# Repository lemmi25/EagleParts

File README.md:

Eagle Parts
===========

In this repo you will find a collection of all my designed PCBs.

# Docu

You can find the [Docu here](https://lemmi25.github.io/EagleParts/).

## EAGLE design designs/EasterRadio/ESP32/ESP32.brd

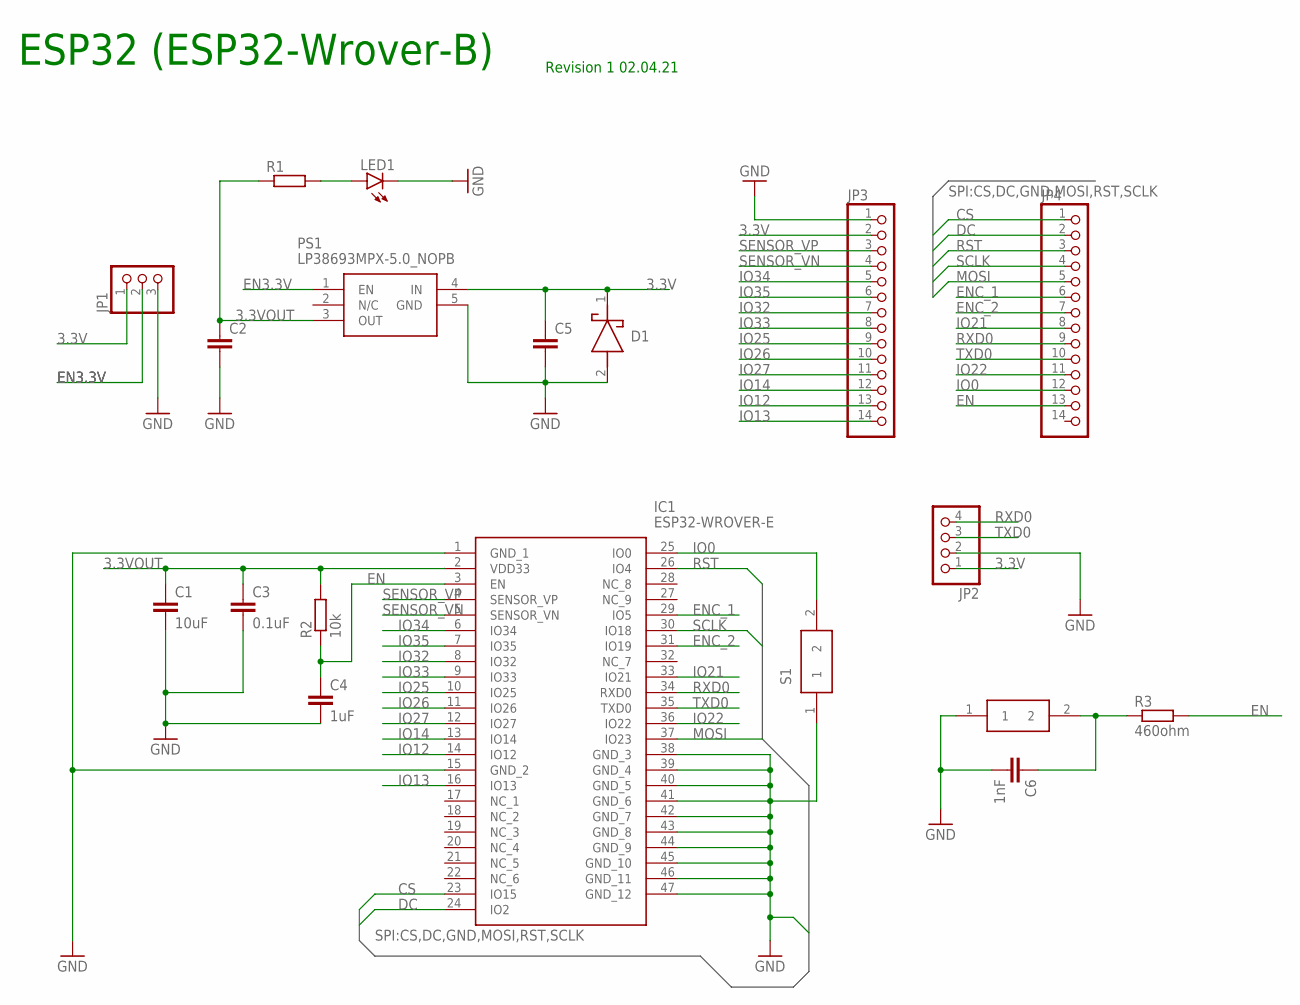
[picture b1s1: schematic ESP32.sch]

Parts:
C1: 10uF; C1206
C2, C5: C-EUC0805; C0805
C3: 0.1uF; C0805
C4: 1uF; C0805
C6: 1nF; C0805
D1: LSM115JE3_TR13; DIOM5436X330N
IC1: ESP32-WROVER-E; ESP32WROVERBM213DH6464PC3Q0
JP1: PINHD-1X3; 1X03
JP2: PINHD-1X4; 1X04
JP3, JP4: PINHD-1X14; 1X14
LED1: LED_1206SMT1206; 1206
PS1: LP38693MPX-5.0_NOPB; SOT150P700X160-5N
R1: R-EU_R0805; R0805
R2: 10k; R0805
R3: 460ohm; R0805
S1, S2: FSMSMTR; FSMSM

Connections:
3.3V: C5.1, D1.1 (K), JP1.1, JP2.1, JP3.2, PS1.4 (IN)
3.3VOUT: C1.1, C2.1, C3.1, IC1.2 (VDD33), PS1.3 (OUT), R1.1, R2.2
CS: IC1.23 (IO15), JP4.1
DC: IC1.24 (IO2), JP4.2
EN: C4.1, IC1.3 (EN), JP4.13, R2.1, R3.2
EN3.3V: JP1.2, PS1.1 (EN)
ENC_1: IC1.29 (IO5), JP4.6
ENC_2: IC1.31 (IO19), JP4.7
EN_1: C6.1, R3.1, S2.2
GND: C1.2, C2.2, C3.2, C4.2, C5.2, C6.2, D1.2 (A), IC1.1 (GND_1), IC1.15 (GND_2), IC1.38 (GND_3), IC1.39 (GND_4), IC1.40 (GND_5), IC1.41 (GND_6), IC1.42 (GND_7), IC1.43 (GND_8), IC1.44 (GND_9), IC1.45 (GND_10), IC1.46 (GND_11), IC1.47 (GND_12), JP1.3, JP2.2, JP3.1, LED1.C, PS1.5 (GND), S1.1, S2.1
IO0: IC1.25 (IO0), JP4.12, S1.2
IO12: IC1.14 (IO12), JP3.13
IO13: IC1.16 (IO13), JP3.14
IO14: IC1.13 (IO14), JP3.12
IO21: IC1.33 (IO21), JP4.8
IO22: IC1.36 (IO22), JP4.11
IO25: IC1.10 (IO25), JP3.9
IO26: IC1.11 (IO26), JP3.10
IO27: IC1.12 (IO27), JP3.11
IO32: IC1.8 (IO32), JP3.7
IO33: IC1.9 (IO33), JP3.8
IO34: IC1.6 (IO34), JP3.5
IO35: IC1.7 (IO35), JP3.6
MOSI: IC1.37 (IO23), JP4.5
unnamed: LED1.A, R1.2
RST: IC1.26 (IO4), JP4.3
RXD0: IC1.34 (RXD0), JP2.4, JP4.9
SCLK: IC1.30 (IO18), JP4.4
SENSOR_VN: IC1.5 (SENSOR_VN), JP3.4
SENSOR_VP: IC1.4 (SENSOR_VP), JP3.3
TXD0: IC1.35 (TXD0), JP2.3, JP4.10

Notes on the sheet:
ESP32 (ESP32-Wrover-B)
Revision 1 02.04.21

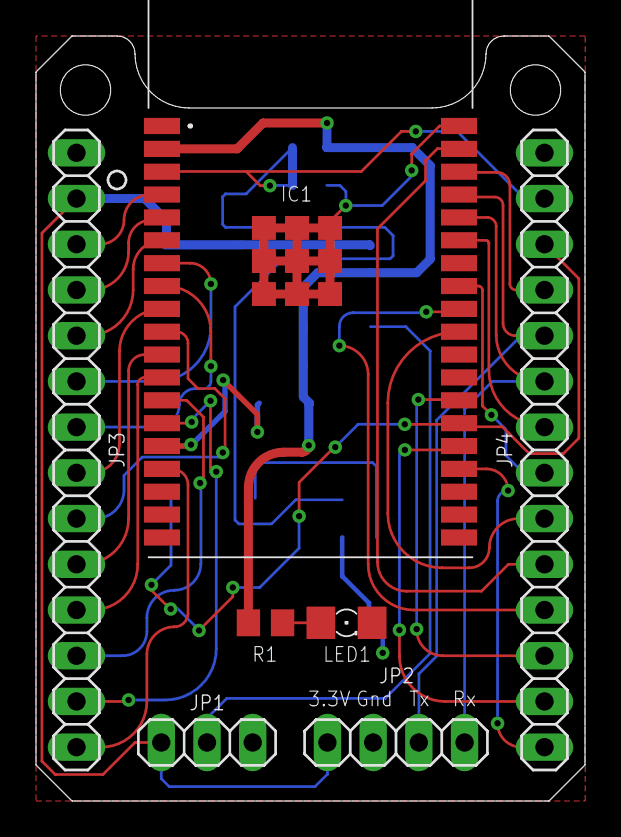
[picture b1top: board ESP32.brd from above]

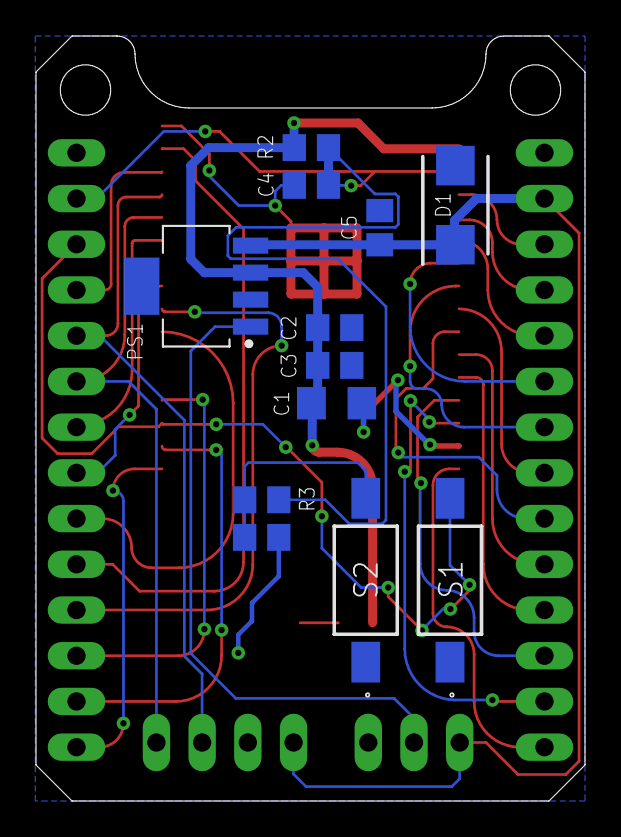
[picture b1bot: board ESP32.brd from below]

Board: 2 copper layers, 30.5 x 42.5 mm, 19 parts (12 on the bottom side), 31 nets.

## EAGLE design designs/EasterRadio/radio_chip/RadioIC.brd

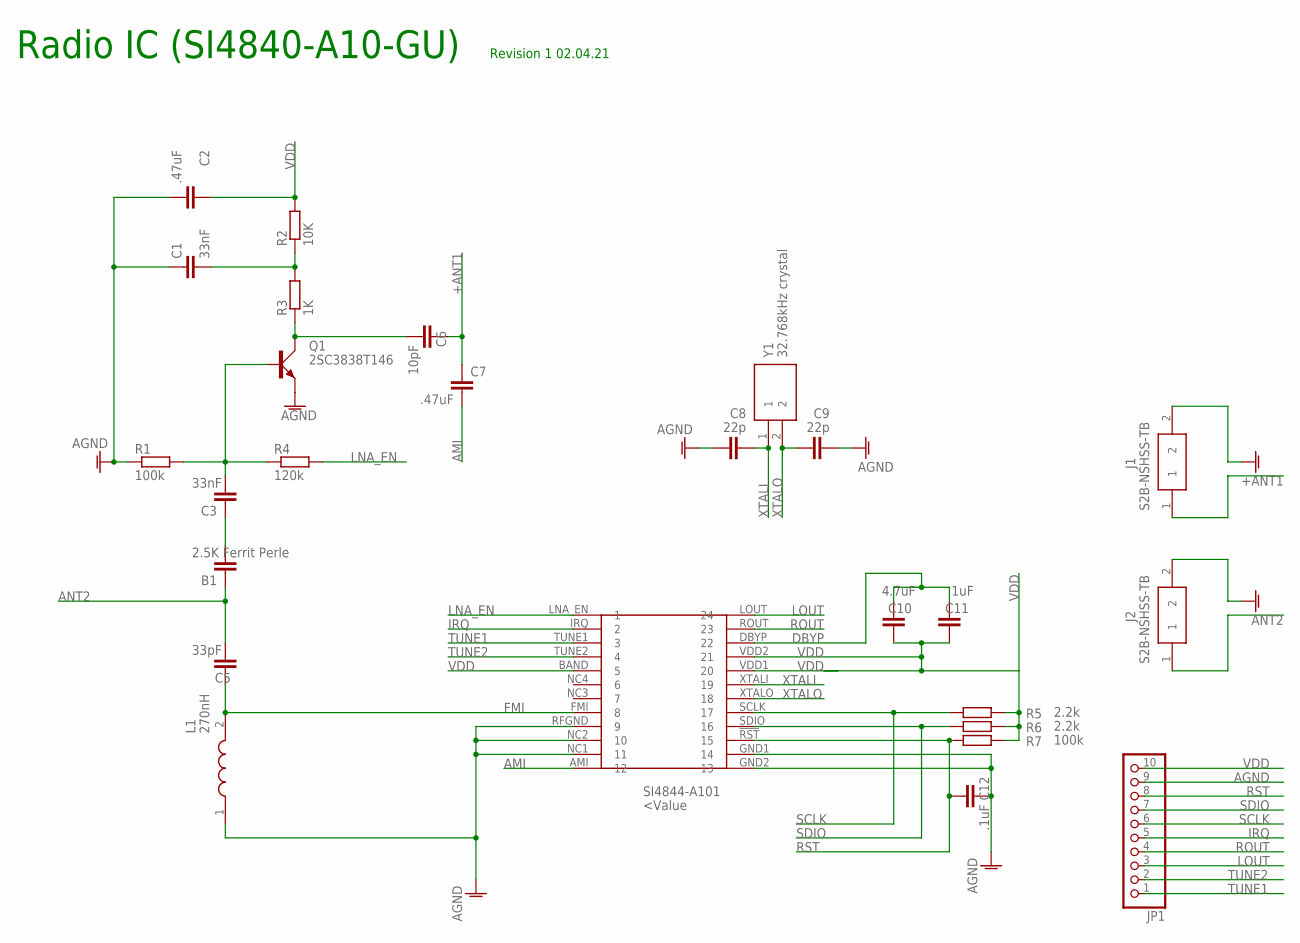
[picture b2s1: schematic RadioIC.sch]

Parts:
B1: 2.5K Ferrit Perle; C0805
C1, C3: 33nF; C1206
C2, C7: .47uF; C0805
C5: 33pF; C0805
C6: 10pF; C0805
C8, C9: 22p; C0805
C10: 4.7uF; C1206
C11: 1uF; C0805
C12: .1uF; C0805
J1, J2: S2B-NSHSS-TB; SM02B-NSHSS-TB
JP1: PINHD-1X10; 1X10
L1: 270nH; LQW2UAS12NG00L
Q1: 2SC3838T146; SC59
R1, R7: 100k; R0805
R2: 10K; R1206
R3: 1K; R1206
R4: 120k; R0805
R5, R6: 2.2k; R0805
SI4844-A101: SI4840-A10-GU; SSOP
Y1: 32.768kHz crystal; CM7VT1A32768KHZ125PF10PPMTBQC

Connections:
+ANT1: C6.1, C7.1, J1.1
AGND: C1.1, C2.2, C8.1, C9.2, C12.1, J1.2, J2.2, JP1.9, L1.1, Q1.E, R1.1, SI4844-A101.GND1 (14), SI4844-A101.GND2 (13), SI4844-A101.NC1 (11), SI4844-A101.NC2 (10), SI4844-A101.RFGND (9)
AMI: C7.2, SI4844-A101.AMI (12)
ANT2: B1.1, C5.2, J2.1
DBYP: C10.2, C11.2, SI4844-A101.DBYP (22)
FMI: C5.1, L1.2, SI4844-A101.FMI (8)
IRQ: JP1.5, SI4844-A101.IRQ (2)
LNA_EN: R4.2, SI4844-A101.LNA_EN (1)
LOUT: JP1.3, SI4844-A101.LOUT (24)
unnamed: B1.2, C3.1
unnamed: C3.2, Q1.B, R1.2, R4.1
unnamed: C6.2, Q1.C, R3.1
unnamed: C1.2, R2.1, R3.2
ROUT: JP1.4, SI4844-A101.ROUT (23)
RST: C12.2, JP1.8, R7.1, SI4844-A101.!RST (15)
SCLK: JP1.6, R5.1, SI4844-A101.SCLK (17)
SDIO: JP1.7, R6.1, SI4844-A101.SDIO (16)
TUNE1: JP1.1, SI4844-A101.TUNE1 (3)
TUNE2: JP1.2, SI4844-A101.TUNE2 (4)
VDD: C2.1, C10.1, C11.1, JP1.10, R2.2, R5.2, R6.2, R7.2, SI4844-A101.BAND (5), SI4844-A101.VDD1 (20), SI4844-A101.VDD2 (21)
XTALI: C8.2, SI4844-A101.XTALI (19), Y1.1
XTALO: C9.1, SI4844-A101.XTALO (18), Y1.2

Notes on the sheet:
Radio IC (SI4840-A10-GU)
Revision 1 02.04.21

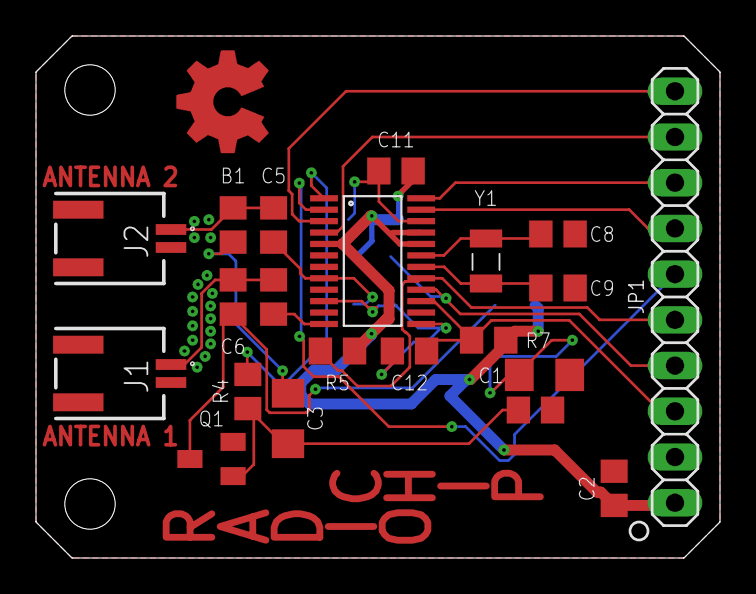
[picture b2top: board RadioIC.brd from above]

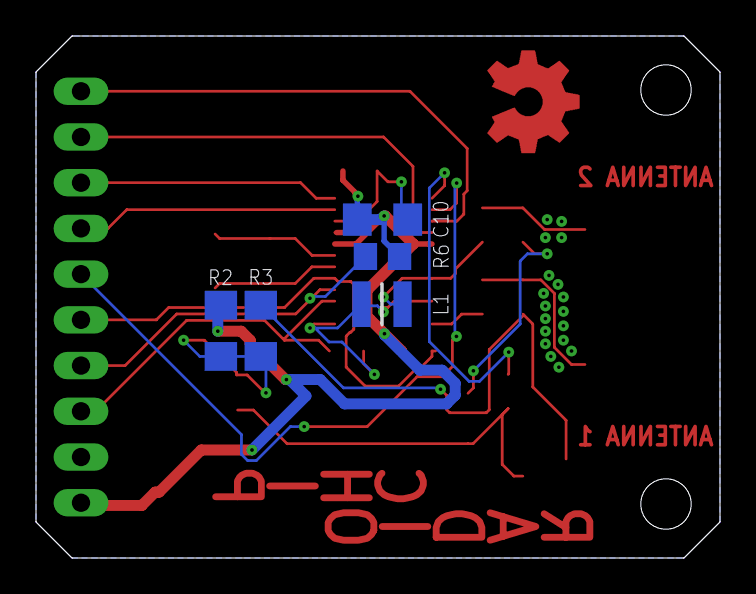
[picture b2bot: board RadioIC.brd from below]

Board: 2 copper layers, 38.0 x 29.0 mm, 26 parts (5 on the bottom side), 22 nets.

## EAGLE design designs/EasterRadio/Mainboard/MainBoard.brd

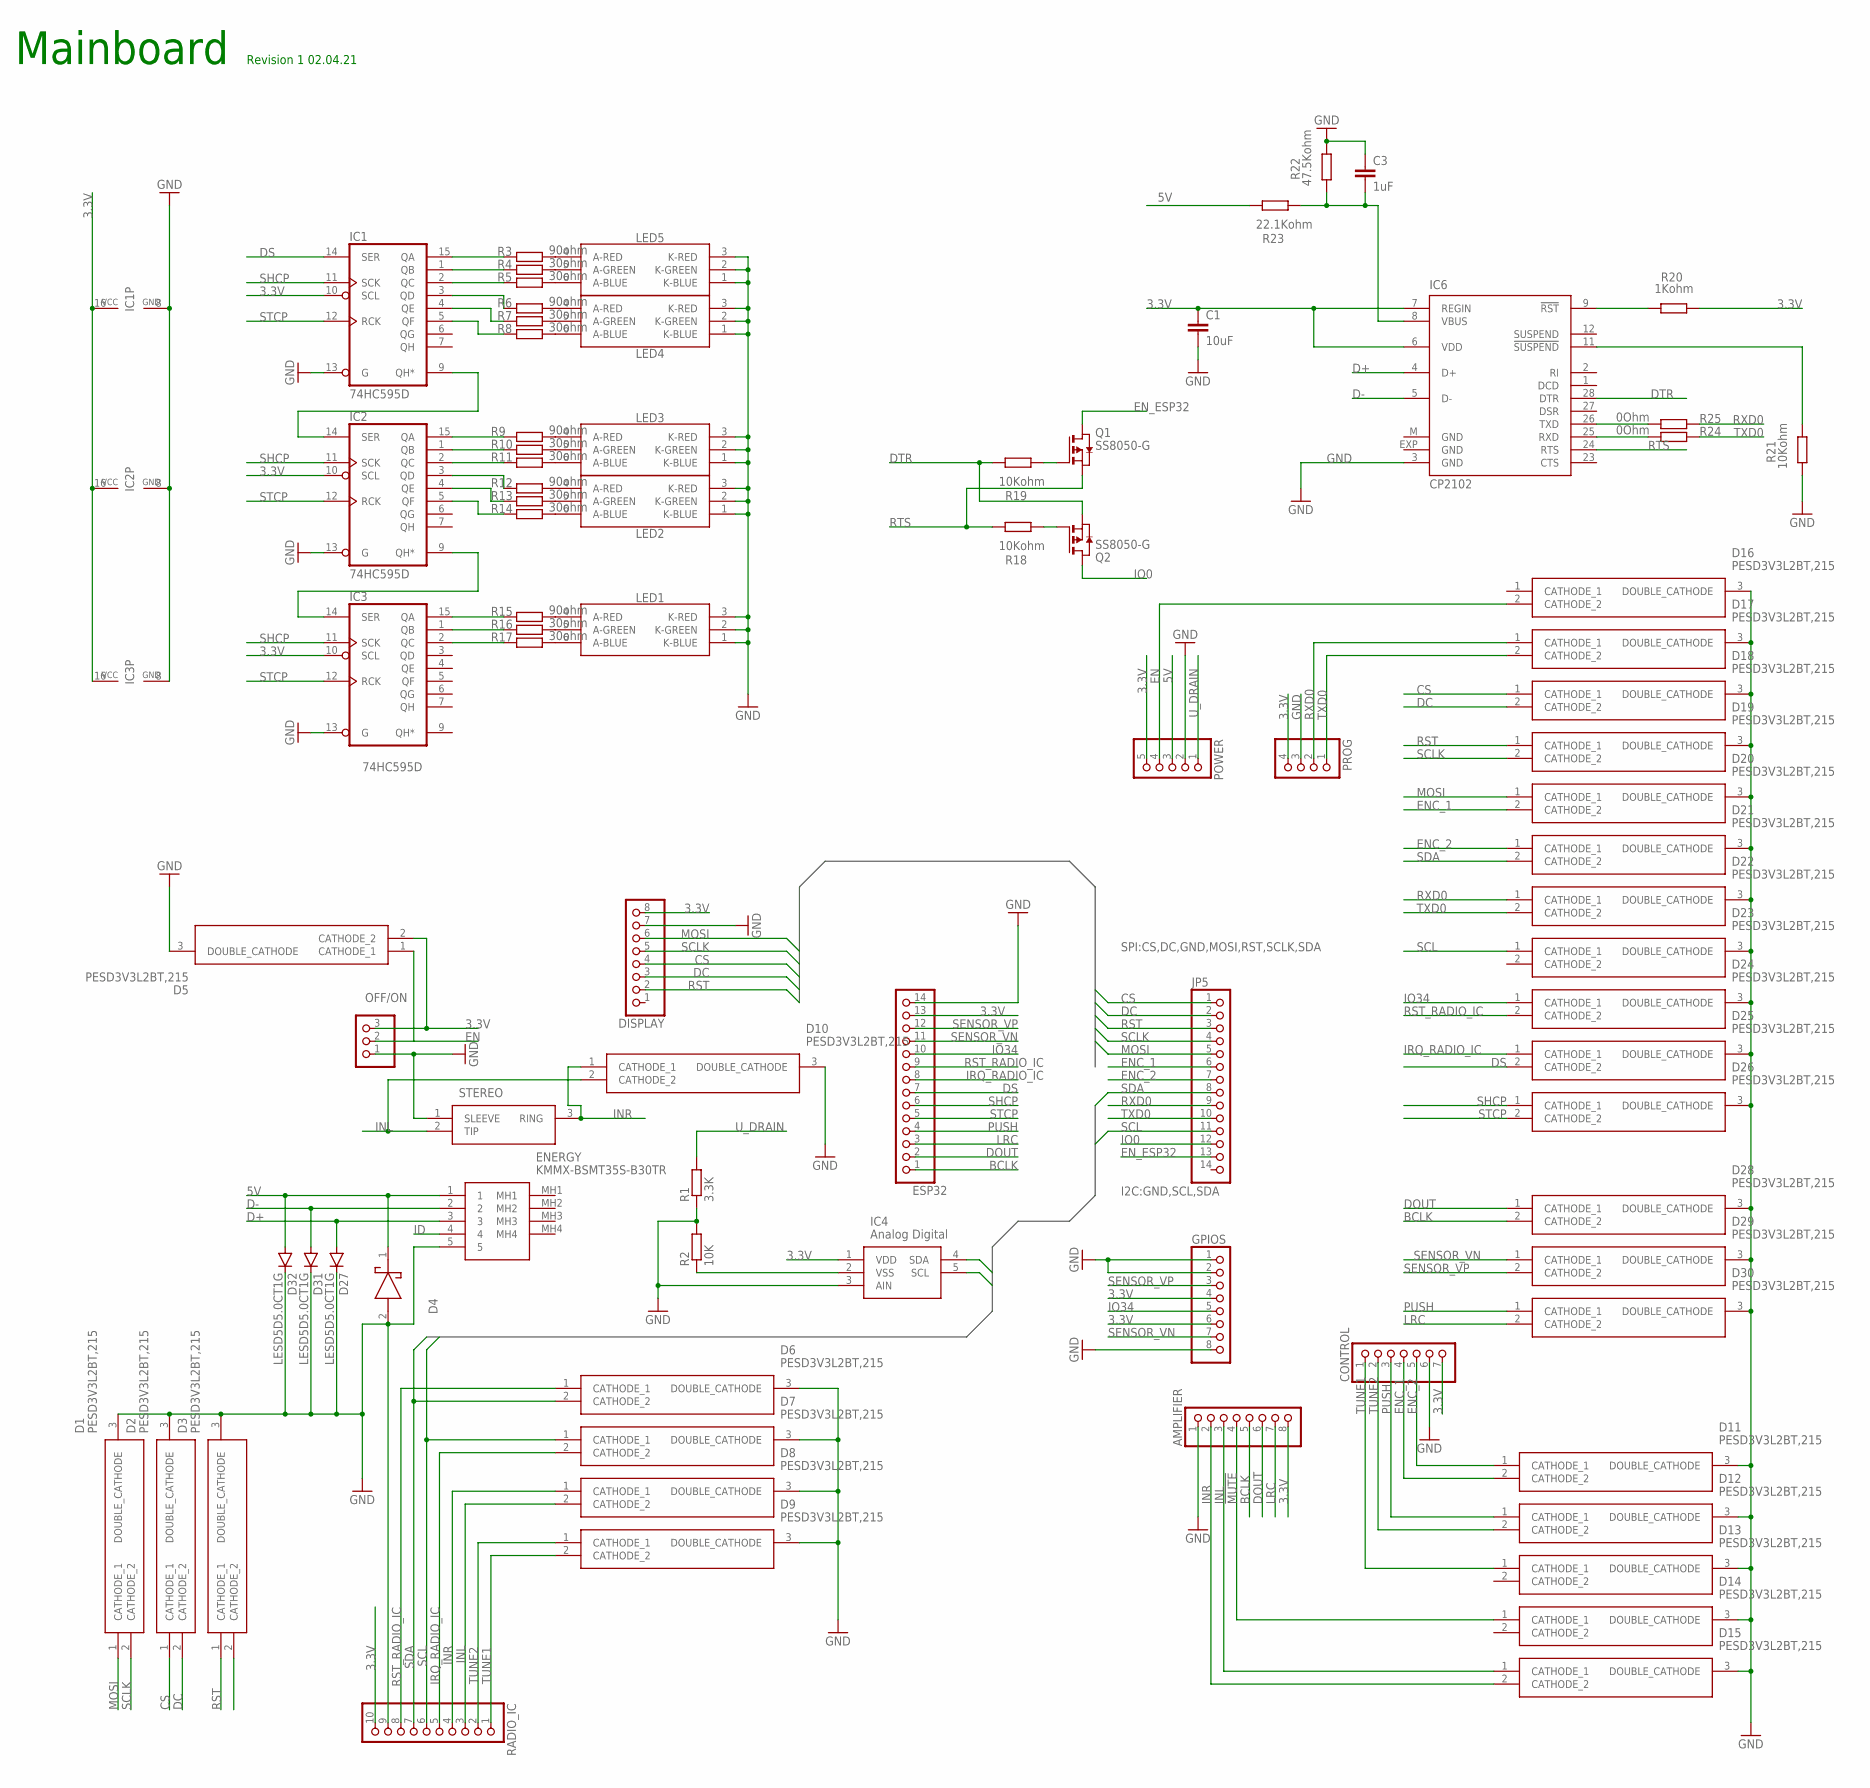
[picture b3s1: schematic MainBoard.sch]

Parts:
AMPLIFIER: PINHD-1X8; 1X08
C1: 10uF; C0805
C3: 1uF; C0805
CONTROL: PINHD-1X7; 1X07
D1, D2, D3, D5, D6, D7, D8, D9, D10, D11, D12, D13, D14, D15, D16, D17, D18, D19, D20, D21, D22, D23, D24, D25, D26, D28, D29, D30: PESD3V3L2BT,215; SOT95P230X110-3N
D4: LSM115JE3_TR13; DIOM5436X330N
D27, D31, D32: LESD5D5.0CT1G; SOD523
DISPLAY: PINHD-1X8; 1X08
ENERGY: KMMX-BSMT35S-B30TR; KMMXBSMT35SB30TR
ESP32: PINHD-1X14; 1X14
GPIOS: PINHD-1X8; 1X08
IC1, IC2, IC3: 74HC595D; SO16
IC4: Analog Digital; SOT95P280X145-5N
IC6: CP2102; MLP28
JP5: PINHD-1X14; 1X14
LED1, LED2, LED3, LED4, LED5: CLY6D-FKC-CK1N1D1BB7D3D3; PLCC6
OFF/ON: PINHD-1X3; 1X03
POWER: PINHD-1X5; 1X05
PROG: PINHD-1X4; 1X04
Q1, Q2: SS8050-G; SOT-23
R1: 3.3K; R0603
R2: 10K; R0603
R3, R6, R9, R12, R15: 90ohm; R0402
R4, R5, R7, R8, R10, R11, R13, R14, R16, R17: 30ohm; R0402
R18, R19: 10Kohm; R0402
R20: 1Kohm; R0402
R21: 10Kohm; R0805
R22: 47.5Kohm; R0402
R23: 22.1Kohm; R0402
R24, R25: 0Ohm; R0603
RADIO_IC: PINHD-1X10; 1X10
STEREO: SJ-3523-SMT-TR; SJ3523SMTTR

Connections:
3.3V: AMPLIFIER.8, C1.1, CONTROL.7, D5.2 (CATHODE_2), DISPLAY.8, ESP32.13, GPIOS.4, GPIOS.6, IC1.10 (SCL), IC1.16 (VCC), IC2.10 (SCL), IC2.16 (VCC), IC3.10 (SCL), IC3.16 (VCC), IC4.1 (VDD), IC6.6 (VDD), IC6.7 (REGIN), OFF/ON.3, POWER.5, PROG.4, R20.2, RADIO_IC.10
5V: D4.1 (K), D32.A, ENERGY.1, POWER.3, R23.1
!MUTE: AMPLIFIER.4, D14.1 (CATHODE_1)
BCLK: AMPLIFIER.5, D28.2 (CATHODE_2), ESP32.1
CS: D2.1 (CATHODE_1), D18.1 (CATHODE_1), DISPLAY.4, JP5.1
D+: D27.A, ENERGY.3, IC6.4 (D+)
D-: D31.A, ENERGY.2, IC6.5 (D-)
DC: D2.2 (CATHODE_2), D18.2 (CATHODE_2), DISPLAY.3, JP5.2
DOUT: AMPLIFIER.6, D28.1 (CATHODE_1), ESP32.2
DS: D25.2 (CATHODE_2), ESP32.7, IC1.14 (SER)
DTR: IC6.28 (DTR), Q2.2 (S), R19.1
EN: D5.1 (CATHODE_1), D16.2 (CATHODE_2), OFF/ON.2, POWER.4
ENC_1: CONTROL.4, D11.2 (CATHODE_2), D20.2 (CATHODE_2), JP5.6
ENC_2: CONTROL.5, D11.1 (CATHODE_1), D21.1 (CATHODE_1), JP5.7
EN_ESP32: JP5.13, Q1.1 (D)
GND: AMPLIFIER.1, C1.2, C3.1, CONTROL.6, D1.3 (DOUBLE_CATHODE), D2.3 (DOUBLE_CATHODE), D3.3 (DOUBLE_CATHODE), D4.2 (A), D5.3 (DOUBLE_CATHODE), D6.3 (DOUBLE_CATHODE), D7.3 (DOUBLE_CATHODE), D8.3 (DOUBLE_CATHODE), D9.3 (DOUBLE_CATHODE), D10.3 (DOUBLE_CATHODE), D11.3 (DOUBLE_CATHODE), D12.3 (DOUBLE_CATHODE), D13.3 (DOUBLE_CATHODE), D14.3 (DOUBLE_CATHODE), D15.3 (DOUBLE_CATHODE), D16.3 (DOUBLE_CATHODE), D17.3 (DOUBLE_CATHODE), D18.3 (DOUBLE_CATHODE), D19.3 (DOUBLE_CATHODE), D20.3 (DOUBLE_CATHODE), D21.3 (DOUBLE_CATHODE), D22.3 (DOUBLE_CATHODE), D23.3 (DOUBLE_CATHODE), D24.3 (DOUBLE_CATHODE), D25.3 (DOUBLE_CATHODE), D26.3 (DOUBLE_CATHODE), D27.C, D28.3 (DOUBLE_CATHODE), D29.3 (DOUBLE_CATHODE), D30.3 (DOUBLE_CATHODE), D31.C, D32.C, DISPLAY.7, ENERGY.5, ESP32.14, GPIOS.1, GPIOS.2, GPIOS.8, IC1.8 (GND), IC1.13 (G), IC2.8 (GND), IC2.13 (G), IC3.8 (GND), IC3.13 (G), IC4.3 (AIN), IC6.3 (GND), IC6.EXP (GND), IC6.M (GND), LED1.1 (K-BLUE), LED1.2 (K-GREEN), LED1.3 (K-RED), LED2.1 (K-BLUE), LED2.2 (K-GREEN), LED2.3 (K-RED), LED3.1 (K-BLUE), LED3.2 (K-GREEN), LED3.3 (K-RED), LED4.1 (K-BLUE), LED4.2 (K-GREEN), LED4.3 (K-RED), LED5.1 (K-BLUE), LED5.2 (K-GREEN), LED5.3 (K-RED), OFF/ON.1, POWER.2, PROG.3, R1.1, R2.2, R21.1, R22.2, RADIO_IC.9, STEREO.1 (SLEEVE)
ID: ENERGY.4
INL: AMPLIFIER.3, D8.2 (CATHODE_2), D10.2 (CATHODE_2), D15.1 (CATHODE_1), RADIO_IC.3, STEREO.2 (TIP)
INR: AMPLIFIER.2, D8.1 (CATHODE_1), D10.1 (CATHODE_1), D15.2 (CATHODE_2), RADIO_IC.4, STEREO.3 (RING)
IO0: JP5.12, Q2.1 (D)
IO34: D24.1 (CATHODE_1), ESP32.10, GPIOS.5
IRQ_RADIO_IC: D7.2 (CATHODE_2), D25.1 (CATHODE_1), ESP32.8, RADIO_IC.5
LRC: AMPLIFIER.7, D30.2 (CATHODE_2), ESP32.3
MOSI: D1.1 (CATHODE_1), D20.1 (CATHODE_1), DISPLAY.6, JP5.5
unnamed: Q2.3 (G), R18.2
unnamed: Q1.3 (G), R19.2
unnamed: LED2.4 (A-RED), R12.2
unnamed: LED1.4 (A-RED), R15.2
unnamed: LED2.5 (A-GREEN), R13.2
unnamed: LED5.4 (A-RED), R3.2
unnamed: LED5.5 (A-GREEN), R4.2
unnamed: LED5.6 (A-BLUE), R5.2
unnamed: LED4.4 (A-RED), R6.2
unnamed: LED4.5 (A-GREEN), R7.2
unnamed: LED4.6 (A-BLUE), R8.2
unnamed: LED2.6 (A-BLUE), R14.2
unnamed: LED3.4 (A-RED), R9.2
unnamed: LED3.5 (A-GREEN), R10.2
unnamed: LED3.6 (A-BLUE), R11.2
unnamed: IC1.9 (QH*), IC2.14 (SER)
unnamed: LED1.5 (A-GREEN), R16.2
unnamed: LED1.6 (A-BLUE), R17.2
unnamed: IC3.2 (QC), R17.1
unnamed: IC2.9 (QH*), IC3.14 (SER)
unnamed: IC4.2 (VSS), R2.1
unnamed: IC3.1 (QB), R16.1
unnamed: IC3.15 (QA), R15.1
unnamed: IC2.3 (QD), R12.1
unnamed: IC2.4 (QE), R13.1
unnamed: IC2.5 (QF), R14.1
unnamed: IC2.2 (QC), R11.1
unnamed: IC2.1 (QB), R10.1
unnamed: IC2.15 (QA), R9.1
unnamed: IC1.15 (QA), R3.1
unnamed: IC1.1 (QB), R4.1
unnamed: IC1.2 (QC), R5.1
unnamed: IC1.3 (QD), R6.1
unnamed: IC1.4 (QE), R7.1
unnamed: IC1.5 (QF), R8.1
unnamed: IC6.9 (!RST), R20.1
unnamed: IC6.11 (!SUSPEND), R21.2
unnamed: C3.2, IC6.8 (VBUS), R22.1, R23.2
unnamed: IC6.26 (TXD), R24.1
unnamed: IC6.25 (RXD), R25.1
PUSH: CONTROL.3, D12.1 (CATHODE_1), D30.1 (CATHODE_1), ESP32.4
RST: D3.1 (CATHODE_1), D19.1 (CATHODE_1), DISPLAY.2, JP5.3
RST_RADIO_IC: D6.1 (CATHODE_1), D24.2 (CATHODE_2), ESP32.9, RADIO_IC.8
RTS: IC6.24 (RTS), Q1.2 (S), R18.1
RXD0: D17.1 (CATHODE_1), D22.1 (CATHODE_1), JP5.9, PROG.2, R24.2
SCL: D7.1 (CATHODE_1), D23.1 (CATHODE_1), IC4.5 (SCL), JP5.11, RADIO_IC.6
SCLK: D1.2 (CATHODE_2), D19.2 (CATHODE_2), DISPLAY.5, JP5.4
SDA: D6.2 (CATHODE_2), D21.2 (CATHODE_2), IC4.4 (SDA), JP5.8, RADIO_IC.7
SENSOR_VN: D29.1 (CATHODE_1), ESP32.11, GPIOS.7
SENSOR_VP: D29.2 (CATHODE_2), ESP32.12, GPIOS.3
SHCP: D26.1 (CATHODE_1), ESP32.6, IC1.11 (SCK), IC2.11 (SCK), IC3.11 (SCK)
STCP: D26.2 (CATHODE_2), ESP32.5, IC1.12 (RCK), IC2.12 (RCK), IC3.12 (RCK)
TUNE1: CONTROL.1, D9.2 (CATHODE_2), D13.1 (CATHODE_1), RADIO_IC.1
TUNE2: CONTROL.2, D9.1 (CATHODE_1), D12.2 (CATHODE_2), RADIO_IC.2
TXD0: D17.2 (CATHODE_2), D22.2 (CATHODE_2), JP5.10, PROG.1, R25.2
U_DRAIN: POWER.1, R1.2

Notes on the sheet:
Mainboard
Revision 1 02.04.21

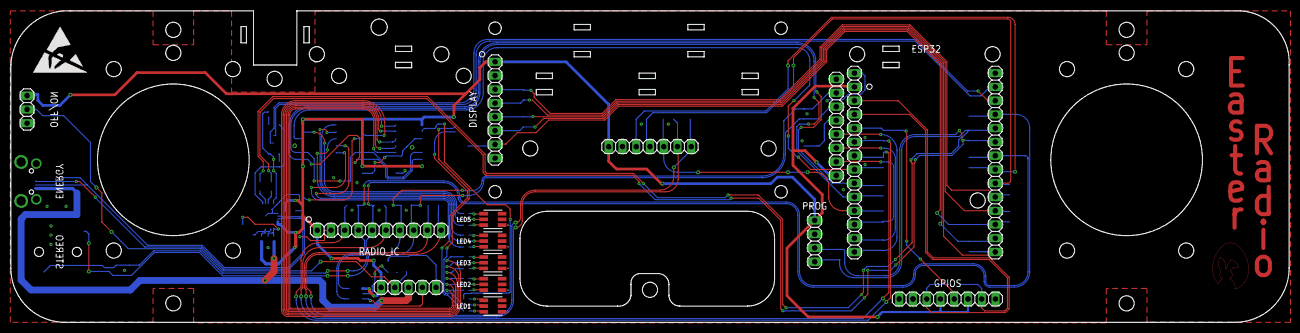
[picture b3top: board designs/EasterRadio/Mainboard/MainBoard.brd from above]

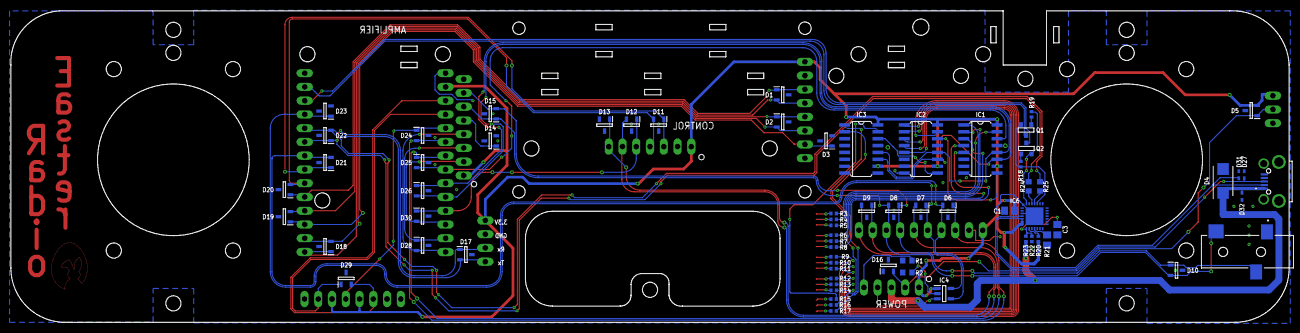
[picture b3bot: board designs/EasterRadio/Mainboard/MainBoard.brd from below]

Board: 2 copper layers, 236.0 x 57.5 mm, 84 parts (68 on the bottom side), 79 nets.

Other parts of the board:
U$1: ESD_10.00

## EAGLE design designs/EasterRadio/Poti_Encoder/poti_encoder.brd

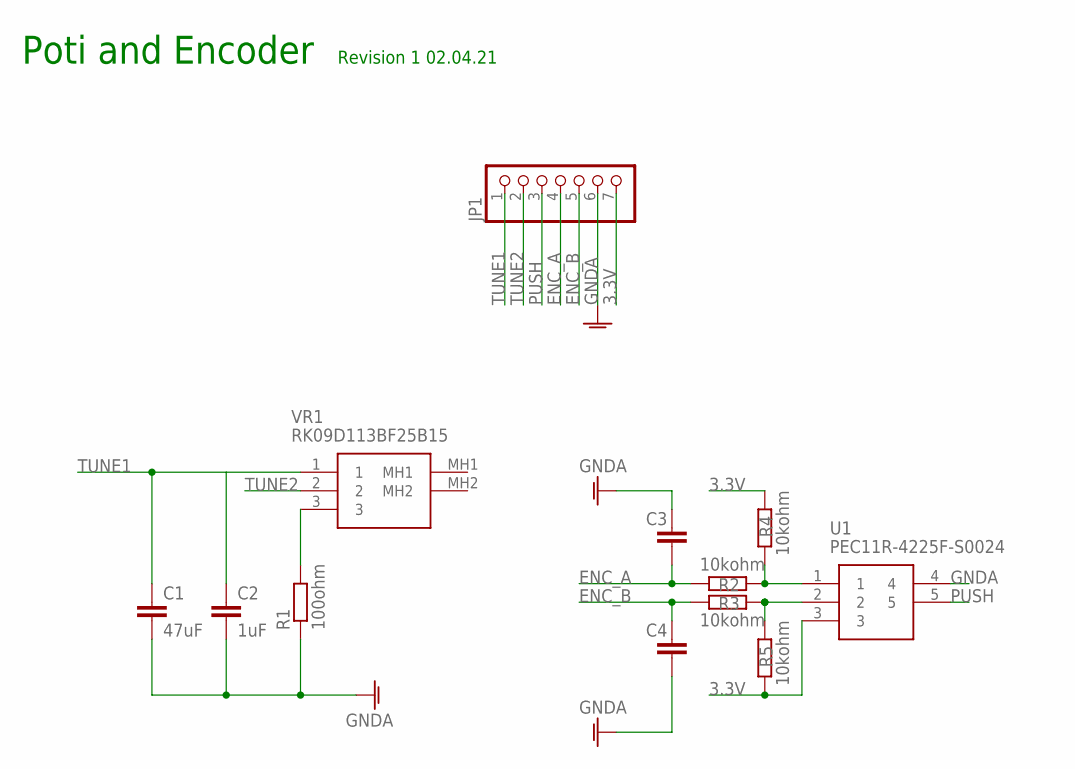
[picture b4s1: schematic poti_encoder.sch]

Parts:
C1: 47uF; C1206
C2: 1uF; C0805
C3, C4: C-EU_805C0805; C0805
JP1: PINHD-1X7; 1X07
R1: 100ohm; R0805
R2, R3, R4, R5: 10kohm; R0805
U1: PEC11R-4225F-S0024; PEC12R-4XXXF-SXXXX_1
VR1: RK09D113BF25B15

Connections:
3.3V: JP1.7, R4.2, R5.1, U1.3
ENC_A: C3.2, JP1.4, R2.1
ENC_B: C4.1, JP1.5, R3.1
GNDA: C1.2, C2.2, C3.1, C4.2, JP1.6, R1.1, U1.4
unnamed: R2.2, R4.1, U1.1
unnamed: R3.2, R5.2, U1.2
unnamed: R1.2, VR1.3
PUSH: JP1.3, U1.5
TUNE1: C1.1, C2.1, JP1.1, VR1.1
TUNE2: JP1.2, VR1.2

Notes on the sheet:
Poti and Encoder
Revision 1 02.04.21

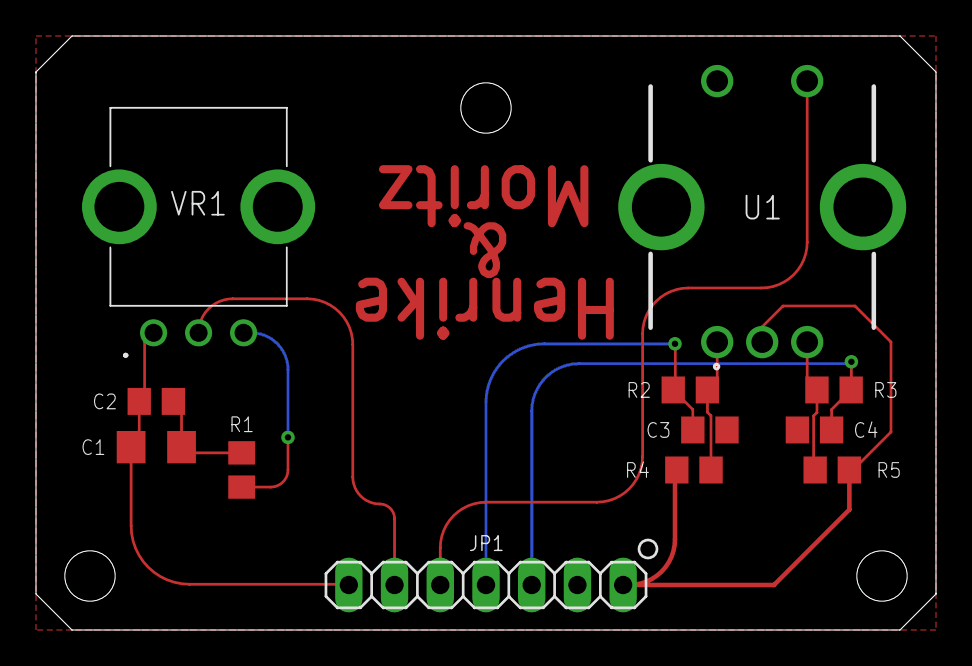
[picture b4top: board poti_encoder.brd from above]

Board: 2 copper layers, 50.0 x 33.0 mm, 12 parts (0 on the bottom side), 10 nets.

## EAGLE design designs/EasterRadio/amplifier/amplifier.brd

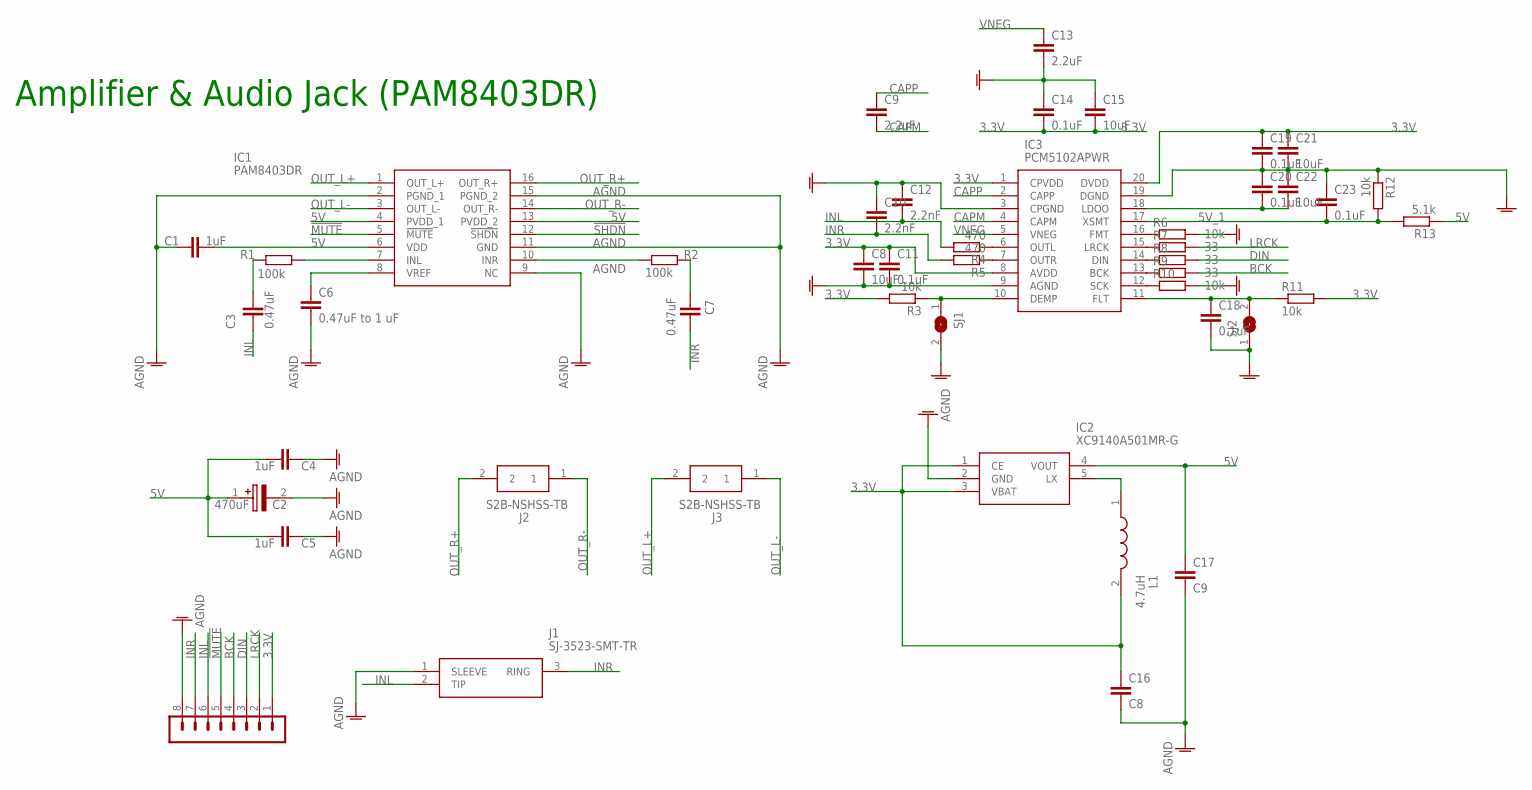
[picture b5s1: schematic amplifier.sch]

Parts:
C1, C4, C5: 1uF; C0805
C2: 470uF; CAPPM7343X430N
C3, C7: 0.47uF; C0805
C6: 0.47uF to 1 uF; C0805
C8, C15: 10uF; C0603
C9, C13: 2.2uF; C0603
C10, C12: 2.2nF; C0603
C11, C14: 0.1uF; C0603
C16: C8; C1206K
C17: C9; C1206K
C18, C19, C20, C23: 0.1uF; C0603K
C21, C22: 10uF; C0603K
IC1: PAM8403DR; SOIC127P605X175-16N
IC2: XC9140A501MR-G; SOT95P280X130-5N
IC3: PCM5102APWR; SOP65P640X120-20N
J1: SJ-3523-SMT-TR; SJ3523SMTTR
J2, J3: S2B-NSHSS-TB; SM02B-NSHSS-TB
JP1: PINHEADER-1X8; MA08-1
L1: 4.7uH; INDPM6060X450N
R1, R2: 100k; R0805
R3, R6, R10, R11, R12: 10k; R0603
R4, R5: 470; R0603
R7, R8, R9: 33; R0603
R13: 5.1k; R0603
SJ1, SJ2: SJ

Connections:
3.3V: C8.1, C11.1, C14.2, C15.2, C16.1, C19.1, C21.1, IC2.1 (CE), IC2.3 (VBAT), IC3.1 (CPVDD), IC3.8 (AVDD), IC3.20 (DVDD), JP1.1, L1.2, R3.2, R11.2
5V: C1.1, C2.1 (+), C4.1, C5.1, C17.1, IC1.4 (PVDD_1), IC1.6 (VDD), IC1.13 (PVDD_2), IC2.4 (VOUT), R13.1
5V_1: C23.2, IC3.17 (XSMT), R12.2, R13.2
!MUTE: IC1.5 (!MUTE), JP1.5
!SHDN: IC1.12 (!SHDN)
AGND: C1.2, C2.2 (-), C4.2, C5.2, C6.2, C8.2, C10.1, C11.2, C12.1, C13.2, C14.1, C15.1, C16.2, C17.2, C18.2, C19.2, C20.1, C21.2, C22.1, C23.1, IC1.2 (PGND_1), IC1.9 (NC), IC1.11 (GND), IC1.15 (PGND_2), IC2.2 (GND), IC3.3 (CPGND), IC3.9 (AGND), IC3.19 (DGND), J1.1 (SLEEVE), JP1.8, R6.2, R10.2, R12.1, SJ1.2, SJ2.1
BCK: JP1.4, R9.2
CAPM: C9.2, IC3.4 (CAPM)
CAPP: C9.1, IC3.2 (CAPP)
DIN: JP1.3, R8.2
IC2_INL: IC1.7 (INL), R1.1
IC2_INR: IC1.10 (INR), R2.1
IC2_VREF: C6.1, IC1.8 (VREF)
INL: C3.1, C12.2, J1.2 (TIP), JP1.6, R4.2
INR: C7.2, C10.2, J1.3 (RING), JP1.7, R5.2
LRCK: JP1.2, R7.2
unnamed: IC2.5 (LX), L1.1
unnamed: IC3.12 (SCK), R10.1
unnamed: IC3.13 (BCK), R9.1
unnamed: IC3.14 (DIN), R8.1
unnamed: IC3.15 (LRCK), R7.1
unnamed: IC3.16 (FMT), R6.1
unnamed: IC3.7 (OUTR), R5.1
unnamed: IC3.6 (OUTL), R4.1
unnamed: C18.1, IC3.11 (FLT), R11.1, SJ2.2
unnamed: C3.2, R1.2
unnamed: C7.1, R2.2
unnamed: IC3.10 (DEMP), R3.1, SJ1.1
unnamed: C20.2, C22.2, IC3.18 (LDOO)
OUT_L+: IC1.1 (OUT_L+), J3.2
OUT_L-: IC1.3 (OUT_L-), J3.1
OUT_R+: IC1.16 (OUT_R+), J2.2
OUT_R-: IC1.14 (OUT_R-), J2.1
VNEG: C13.1, IC3.5 (VNEG)

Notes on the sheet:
Amplifier & Audio Jack (PAM8403DR)

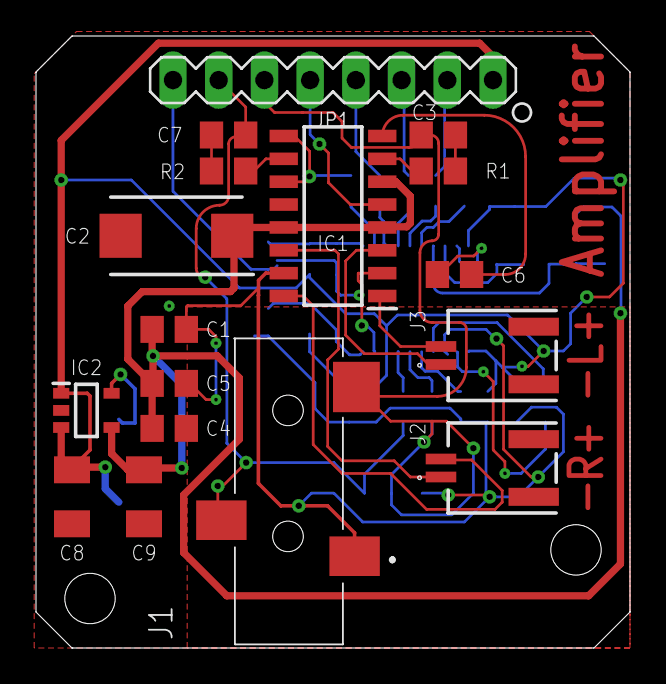
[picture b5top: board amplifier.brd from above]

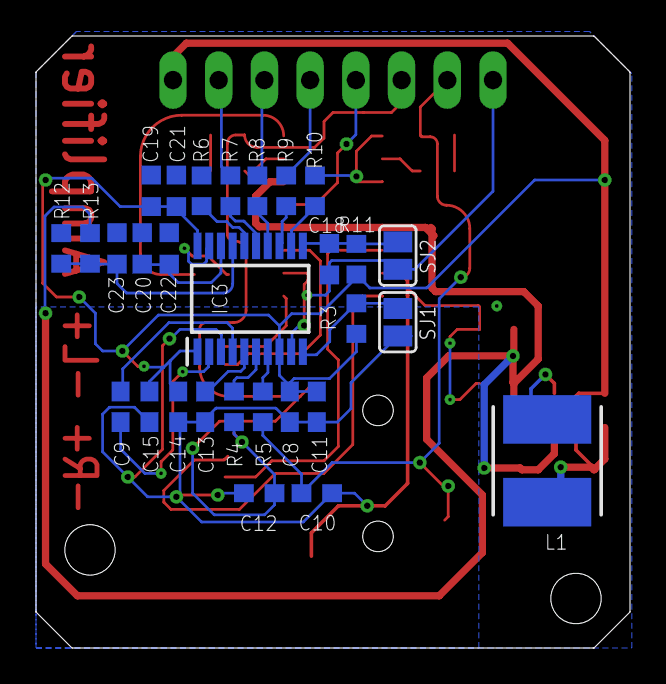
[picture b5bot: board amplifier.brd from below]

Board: 2 copper layers, 33.0 x 34.0 mm, 46 parts (29 on the bottom side), 33 nets.

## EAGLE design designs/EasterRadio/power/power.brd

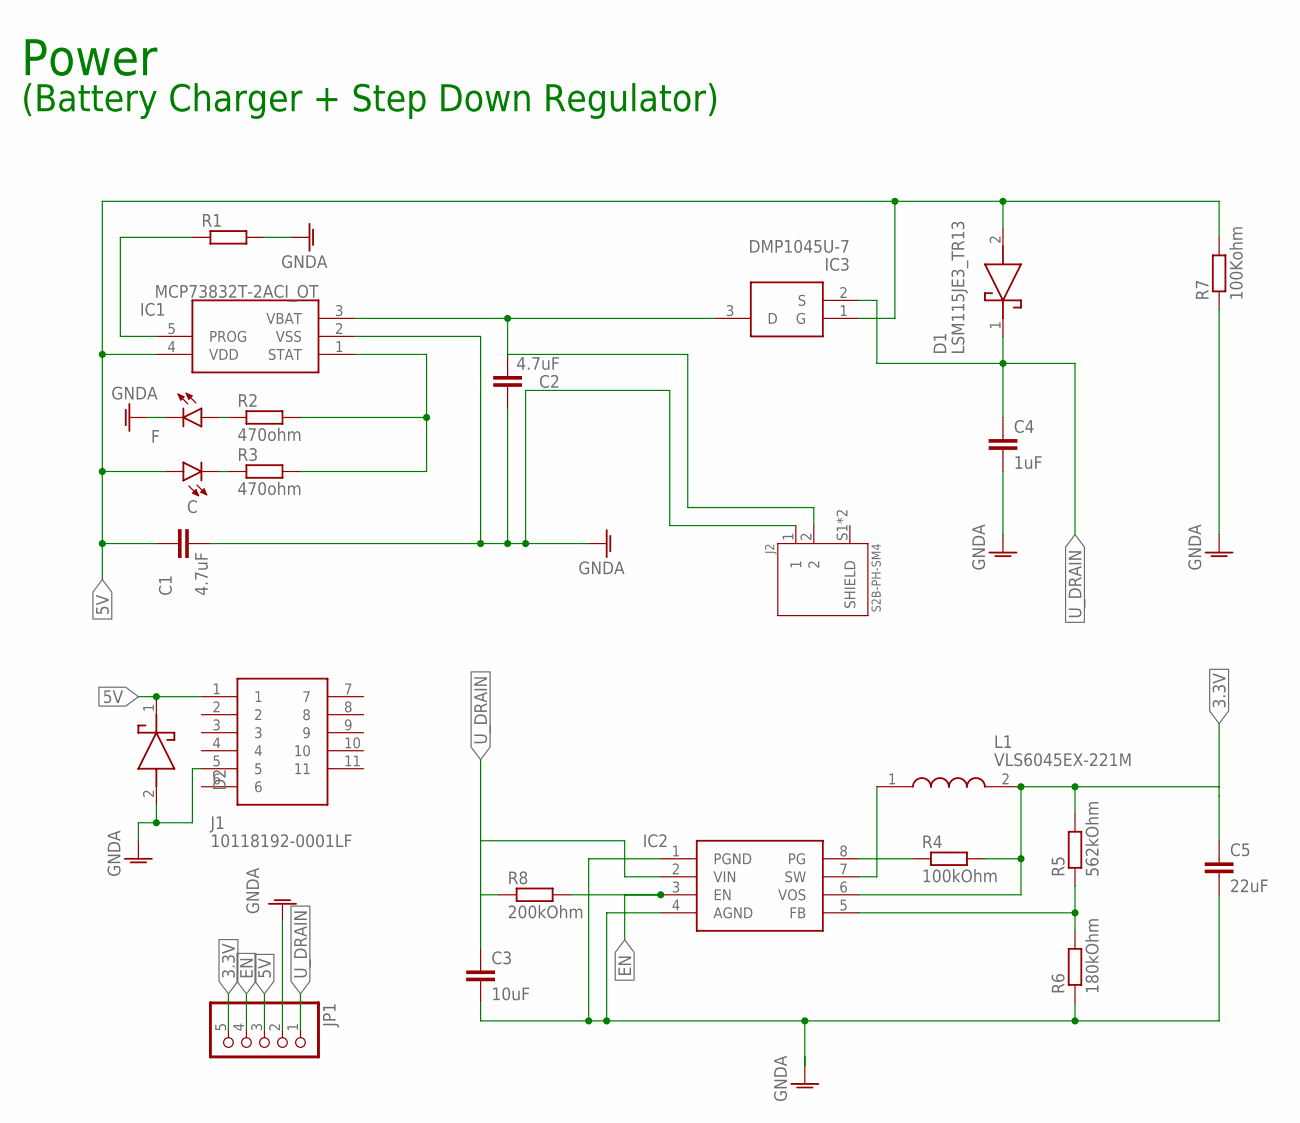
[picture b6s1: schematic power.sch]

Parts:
C: LED_1206SMT1206; 1206
C1, C2: 4.7uF; C1206
C3: 10uF; C1206
C4: 1uF; C0805
C5: 22uF; C0805K
D1, D2: LSM115JE3_TR13; DIOM5436X330N
F: LED_1206SMT1206; 1206
IC1: MCP73832T-2ACI_OT; SOT95P270X145-5N
IC2: TPS62160DGKR; SOP65P490X110-8N
IC3: DMP1045U-7; SOT96P240X100-3N
J1: 10118192-0001LF; 101181920001LF
J2: S2B-PH-SM4; JST_S2B-PH-SM4-TB(LF)(SN)
JP1: PINHD-1X5; 1X05
L1: VLS6045EX-221M; INDPM6060X450N
R1: R-EU_805R0805; R0805
R2, R3: 470ohm; R0805
R4: 100kOhm; R0805
R5: 562kOhm; R0805
R6: 180kOhm; R0805
R7: 100Kohm; R0805
R8: 200kOhm; R0805

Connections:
3.3V: C5.1, IC2.6 (VOS), JP1.5, L1.2, R4.2, R5.2
5V: C.A, C1.1, D1.2 (A), D2.1 (K), IC1.4 (VDD), IC3.1 (G), J1.1, JP1.3, R7.2
EN: IC2.3 (EN), JP1.4, R8.2
FB: IC2.5 (FB), R5.1, R6.2
GNDA: C1.2, C2.1, C3.2, C4.2, C5.2, D2.2 (A), F.C, IC1.2 (VSS), IC2.1 (PGND), IC2.4 (AGND), J1.5, J2.1, JP1.2, R1.2, R6.1, R7.1
unnamed: IC1.5 (PROG), R1.1
unnamed: F.A, R2.1
unnamed: C.C, R3.1
PG: IC2.8 (PG), R4.1
STAT: IC1.1 (STAT), R2.2, R3.2
SW: IC2.7 (SW), L1.1
U_DRAIN: C3.1, C4.1, D1.1 (K), IC2.2 (VIN), IC3.2 (S), JP1.1, R8.1
VBAT: C2.2, IC1.3 (VBAT), IC3.3 (D), J2.2

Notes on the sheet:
Power
(Battery Charger + Step Down Regulator)

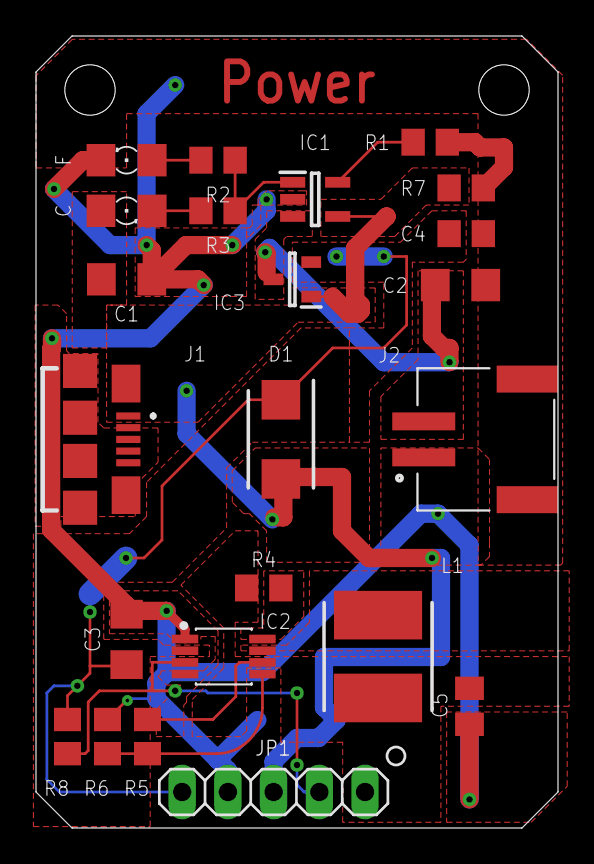
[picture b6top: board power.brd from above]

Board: 2 copper layers, 29.0 x 44.0 mm, 24 parts (1 on the bottom side), 13 nets.
